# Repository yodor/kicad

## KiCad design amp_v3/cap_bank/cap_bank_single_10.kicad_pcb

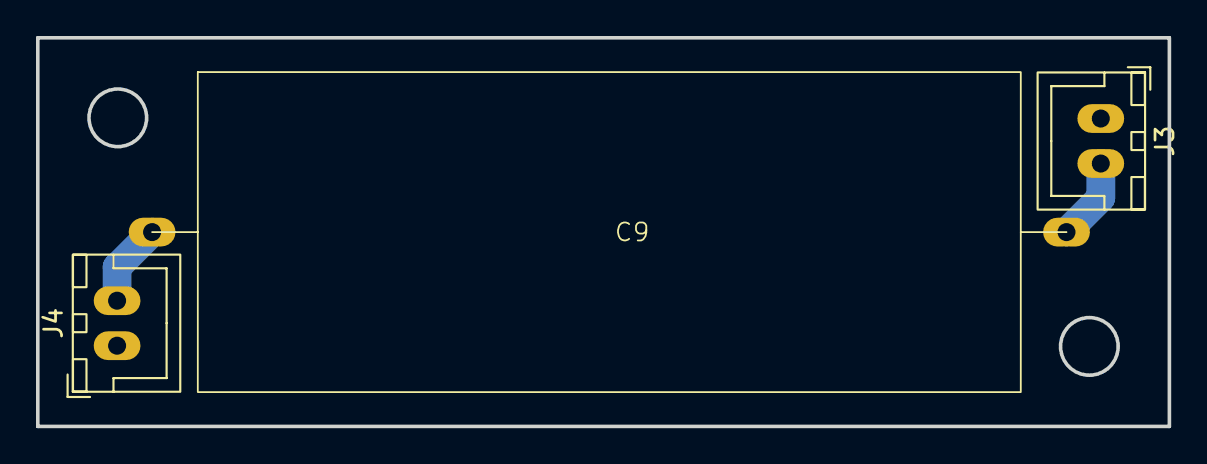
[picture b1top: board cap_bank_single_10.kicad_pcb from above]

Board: 2 copper layers, 62.9 x 21.6 mm, 3 parts (0 on the bottom side), 3 nets.

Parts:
C9: 10uF PP; 10uF - D18 - W46
J3: CAP_IN; JST_XH_B2B-XH-A_1x02_P2.50mm_Vertical
J4: CAP_OUT; JST_XH_B2B-XH-A_1x02_P2.50mm_Vertical

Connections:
/IN: C9.1, J3.2
/OUT: C9.2, J4.2
GNDA: J3.1, J4.1

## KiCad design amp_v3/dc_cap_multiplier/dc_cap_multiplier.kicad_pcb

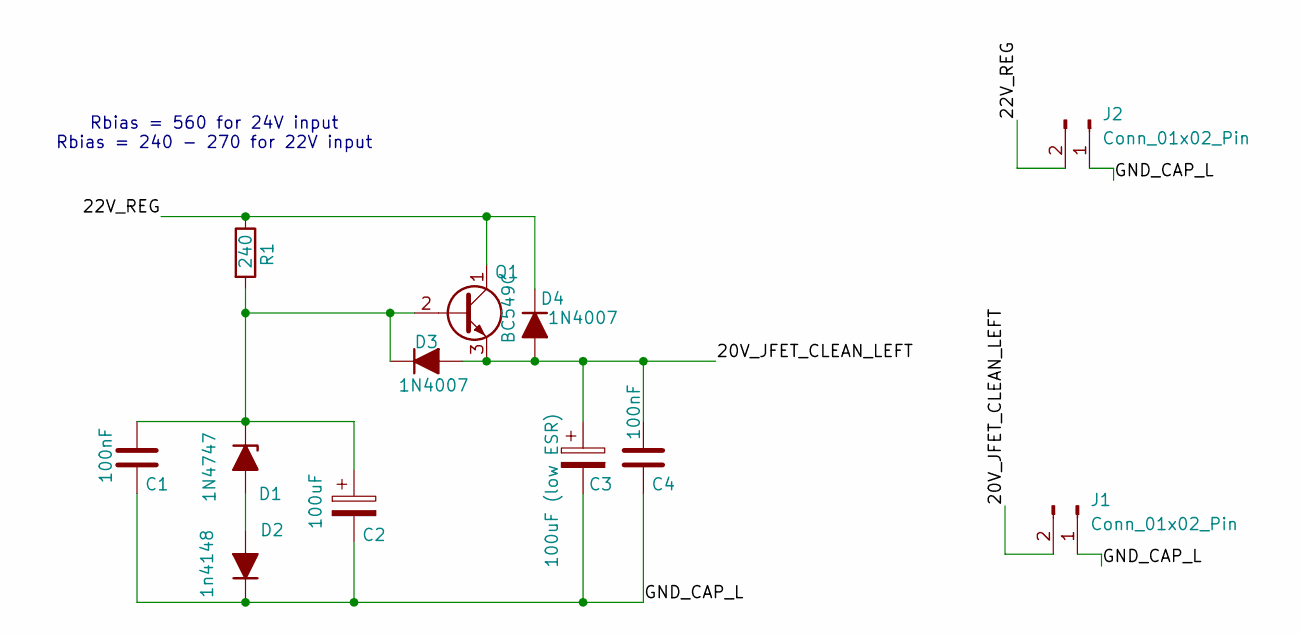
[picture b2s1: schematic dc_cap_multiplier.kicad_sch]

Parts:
C1, C4: 100nF; C_Rect_L7.0mm_W2.5mm_P5.00mm
C2: 100uF; CP_Radial_D6.3mm_P2.50mm
C3: 100uF (low ESR); CP_Radial_D5.0mm_P2.50mm
D1: 1N4747; D_A-405_P10.16mm_Horizontal
D2: 1n4148; D_A-405_P10.16mm_Horizontal
D3, D4: 1N4007; D_A-405_P10.16mm_Horizontal
J1, J2: Conn_01x02_Pin; JST_XH_B2B-XH-A_1x02_P2.50mm_Vertical
Q1: BC549C; TO-92_Inline_Wide
R1: 240; R_Axial_DIN0207_L6.3mm_D2.5mm_P7.62mm_Horizontal

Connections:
/20V_JFET_CLEAN_LEFT: C3.1, C4.1, D3.2 (A), D4.2 (A), J1.2, Q1.3 (E)
/22V_REG: D4.1 (K), J2.2, Q1.1 (C), R1.1
/GND_CAP_L: C1.2, C2.2, C3.2, C4.2, D2.1 (K), J1.1, J2.1
unnamed: D1.2 (A), D2.2 (A)
unnamed: C1.1, C2.1, D1.1 (K), D3.1 (K), Q1.2 (B), R1.2

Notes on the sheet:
Rbias = 560 for 24V input Rbias = 240 - 270 for 22V input

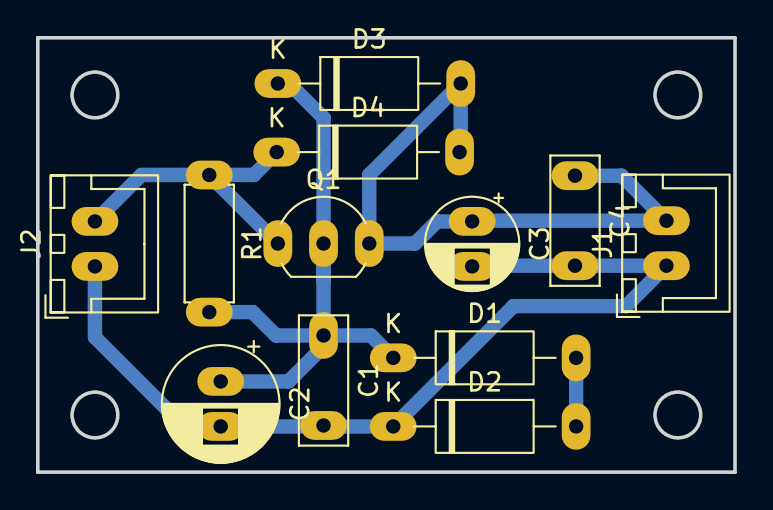
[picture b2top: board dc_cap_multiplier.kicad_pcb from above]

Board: 2 copper layers, 38.7 x 24.1 mm, 12 parts (0 on the bottom side), 5 nets.

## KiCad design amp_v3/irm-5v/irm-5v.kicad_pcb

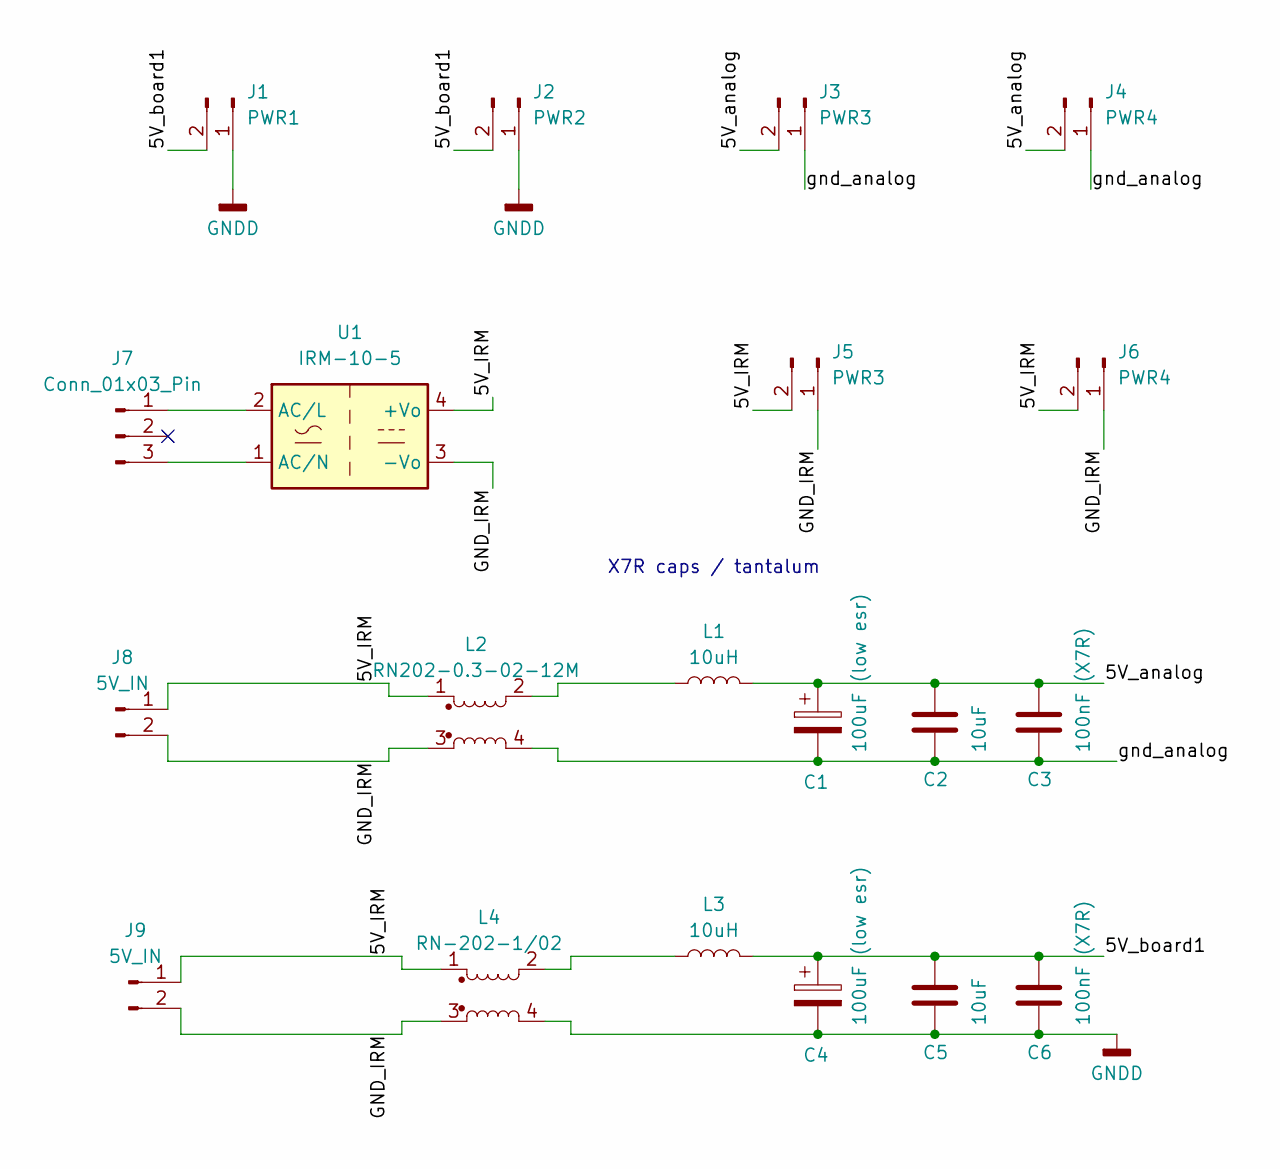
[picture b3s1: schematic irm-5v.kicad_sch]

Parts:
C1, C4: 100uF (low esr); CP_Radial_D6.3mm_P2.50mm
C2, C5: 10uF; C_Disc_D5.0mm_W2.5mm_P5.00mm
C3, C6: 100nF (X7R); C_Disc_D5.0mm_W2.5mm_P5.00mm
J1: PWR1; JST_XH_B2B-XH-A_1x02_P2.50mm_Vertical
J2: PWR2; JST_XH_B2B-XH-A_1x02_P2.50mm_Vertical
J3, J5: PWR3; JST_XH_B2B-XH-A_1x02_P2.50mm_Vertical
J4, J6: PWR4; JST_XH_B2B-XH-A_1x02_P2.50mm_Vertical
J7: Conn_01x03_Pin; JST_XH_B3B-XH-A_1x03_P2.50mm_Vertical
J8, J9: 5V_IN; JST_XH_B2B-XH-A_1x02_P2.50mm_Vertical
L1, L3: 10uH; L_Radial_D7.8mm_P5.00mm_Fastron_07HCP
L2: RN202-0.3-02-12M; Choke_Schaffner_RN202-04-8.8x18.2mm
L4: RN-202-1/02; Choke_Schaffner_RN202-04-8.8x18.2mm
U1: IRM-10-5; Converter_ACDC_MeanWell_IRM-10-xx_THT

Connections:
/5V power/5V_IRM: J5.2, J6.2, J8.1, J9.1, L2.1, L4.1, U1.4 (+Vo)
/5V power/5V_analog: C1.1, C2.1, C3.1, J3.2, J4.2, L1.2
/5V power/5V_board1: C4.1, C5.1, C6.1, J1.2, J2.2, L3.2
/5V power/GND_IRM: J5.1, J6.1, J8.2, J9.2, L2.3, L4.3, U1.3 (-Vo)
/5V power/gnd_analog: C1.2, C2.2, C3.2, J3.1, J4.1, L2.4
GNDD: C4.2, C5.2, C6.2, J1.1, J2.1, L4.4
unnamed: J7.1, U1.2 (AC/L)
unnamed: J7.3, U1.1 (AC/N)
unnamed: L1.1, L2.2
unnamed: L3.1, L4.2

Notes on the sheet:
X7R caps / tantalum

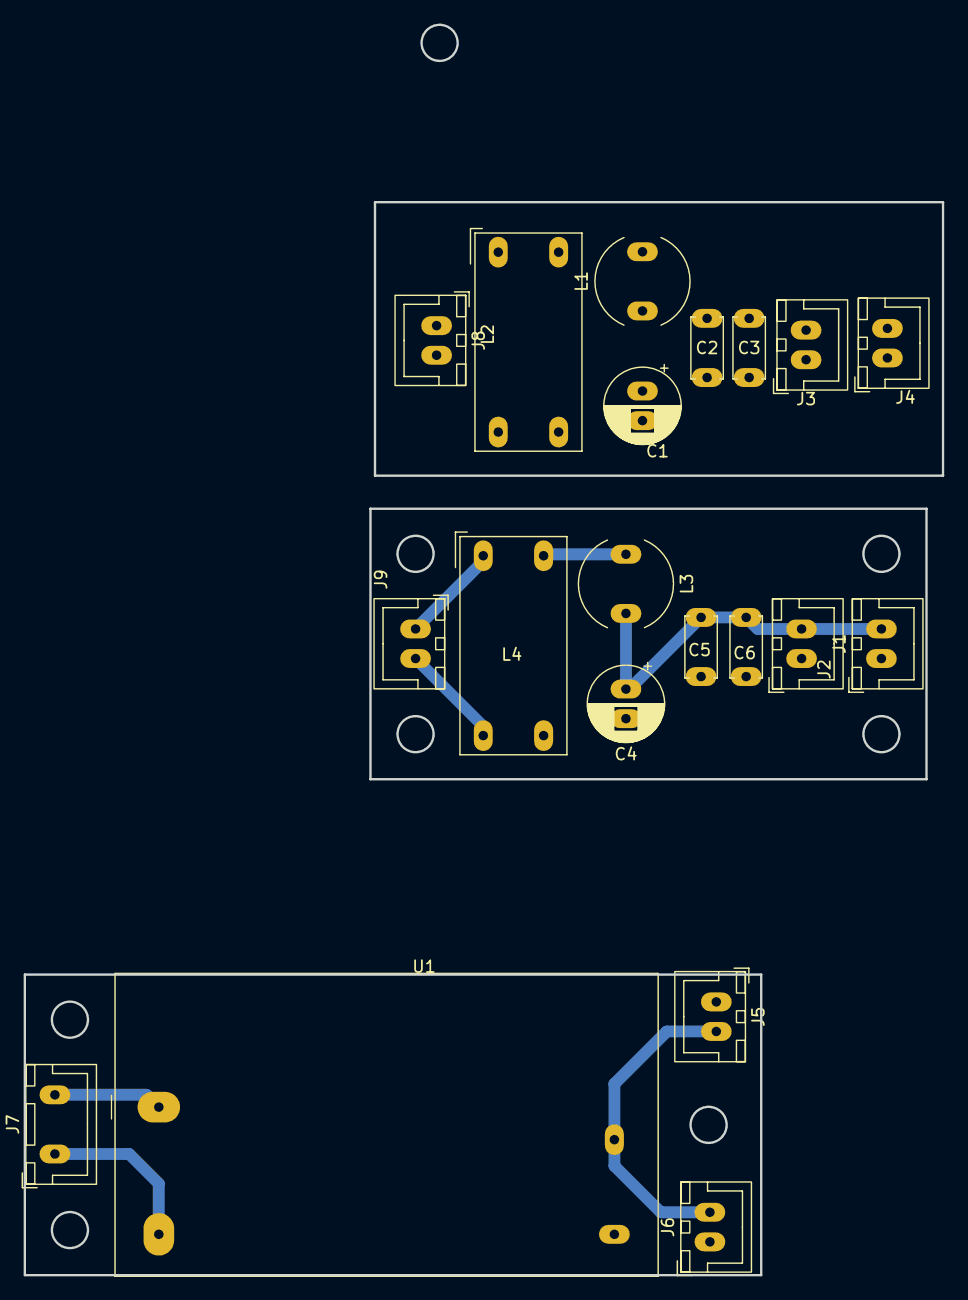
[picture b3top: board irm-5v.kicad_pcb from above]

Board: 2 copper layers, 77.6 x 105.7 mm, 20 parts (0 on the bottom side), 10 nets.

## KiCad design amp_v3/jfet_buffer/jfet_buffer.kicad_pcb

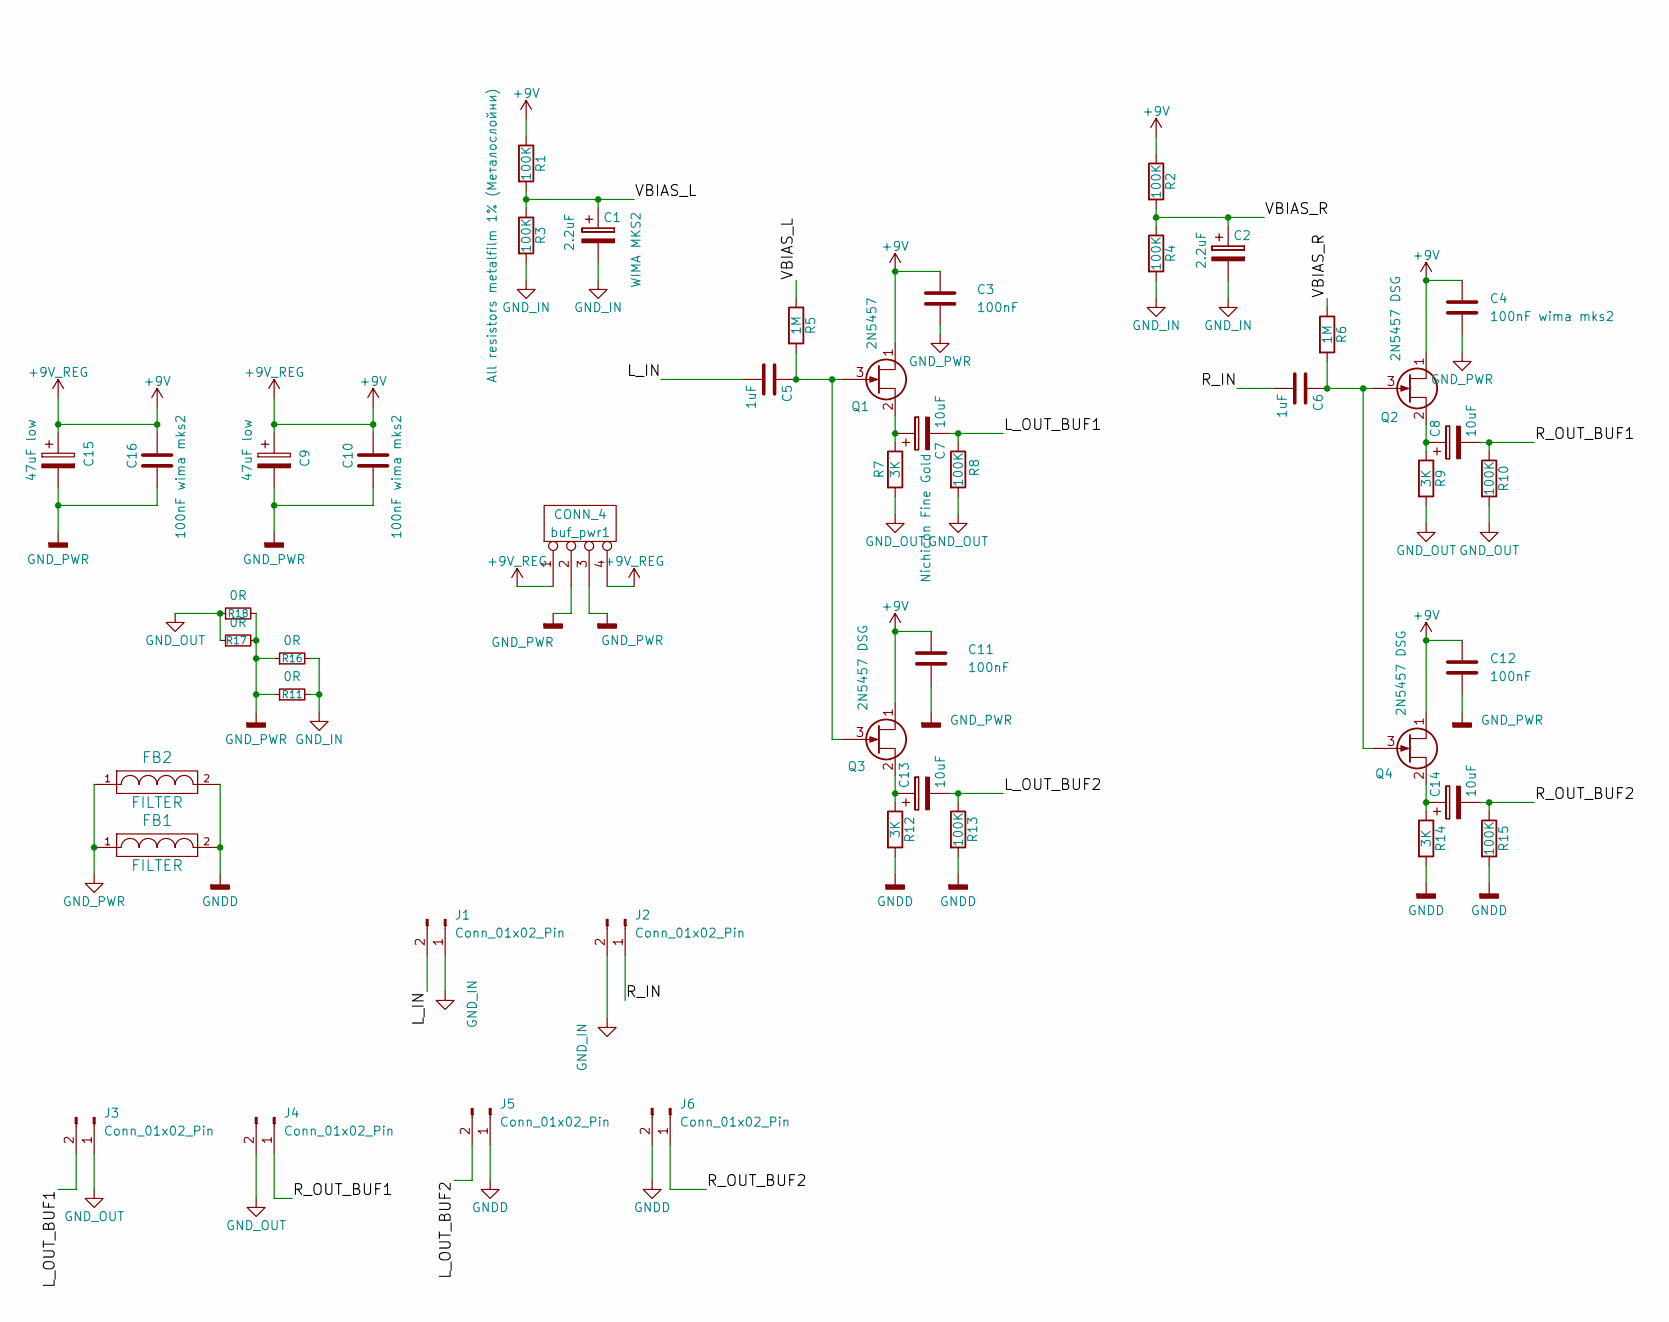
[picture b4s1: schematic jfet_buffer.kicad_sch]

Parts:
C1, C2: 2.2uF; C_Rect_L7.2mm_W7.2mm_P5.00mm_FKS2_FKP2_MKS2_MKP2
C3, C11, C12: 100nF; C_Rect_L7.2mm_W2.5mm_P5.00mm_FKS2_FKP2_MKS2_MKP2
C4, C10, C16: 100nF wima mks2; C_Rect_L7.2mm_W2.5mm_P5.00mm_FKS2_FKP2_MKS2_MKP2
C5, C6: 1uF; C_Rect_L7.2mm_W3.5mm_P5.00mm_FKS2_FKP2_MKS2_MKP2
C7, C8, C13, C14: 10uF; CP_Radial_D5.0mm_P2.50mm
C9, C15: 47uF low; CP_Radial_D5.0mm_P2.50mm
FB1, FB2: FILTER; R_Axial_DIN0309_L9.0mm_D3.2mm_P12.70mm_Horizontal
J1, J2, J3, J4, J5, J6: Conn_01x02_Pin; JST_XH_B2B-XH-A_1x02_P2.50mm_Vertical
Q1: 2N5457; TO-92L_Inline_Wide
Q2, Q3, Q4: 2N5457 DSG; TO-92L_Inline_Wide
R1, R2, R3, R4, R8, R10, R13, R15: 100K; R_Axial_DIN0309_L9.0mm_D3.2mm_P12.70mm_Horizontal
R5, R6: 1M; R_Axial_DIN0309_L9.0mm_D3.2mm_P12.70mm_Horizontal
R7, R9, R12, R14: 3K; R_Axial_DIN0309_L9.0mm_D3.2mm_P12.70mm_Horizontal
R11, R16, R17, R18: 0R; R_Axial_DIN0309_L9.0mm_D3.2mm_P12.70mm_Horizontal
buf_pwr1: CONN_4; JST_XH_B4B-XH-A_1x04_P2.50mm_Vertical

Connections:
+9V: C3.1, C4.1, C9.1, C10.1, C11.1, C12.1, C15.1, C16.1, Q1.1 (D), Q2.1 (D), Q3.1 (D), Q4.1 (D), R1.1, R2.1, buf_pwr1.1, buf_pwr1.4
/L_IN: C5.2, J1.2
/L_OUT_BUF1: C7.2, J3.2, R8.1
/L_OUT_BUF2: C13.2, J5.2, R13.1
/R_IN: C6.2, J2.1
/R_OUT_BUF1: C8.2, J4.1, R10.1
/R_OUT_BUF2: C14.2, J6.1, R15.1
/VBIAS_L: C1.1, R1.2, R3.1, R5.1
/VBIAS_R: C2.1, R2.2, R4.1, R6.1
GNDD: FB1.2, FB2.2, J5.1, J6.2, R12.2, R13.2, R14.2, R15.2
GND_IN: C1.2, C2.2, J1.1, J2.2, R3.2, R4.2, R11.2, R16.2
GND_OUT: J3.1, J4.2, R7.2, R8.2, R9.2, R10.2, R17.1, R18.1
GND_PWR: C3.2, C4.2, C9.2, C10.2, C11.2, C12.2, C15.2, C16.2, FB1.1, FB2.1, R11.1, R16.1, R17.2, R18.2, buf_pwr1.2, buf_pwr1.3
unnamed: C5.1, Q1.3 (G), Q3.3 (G), R5.2
unnamed: C7.1, Q1.2 (S), R7.1
unnamed: C6.1, Q2.3 (G), Q4.3 (G), R6.2
unnamed: C8.1, Q2.2 (S), R9.1
unnamed: C13.1, Q3.2 (S), R12.1
unnamed: C14.1, Q4.2 (S), R14.1

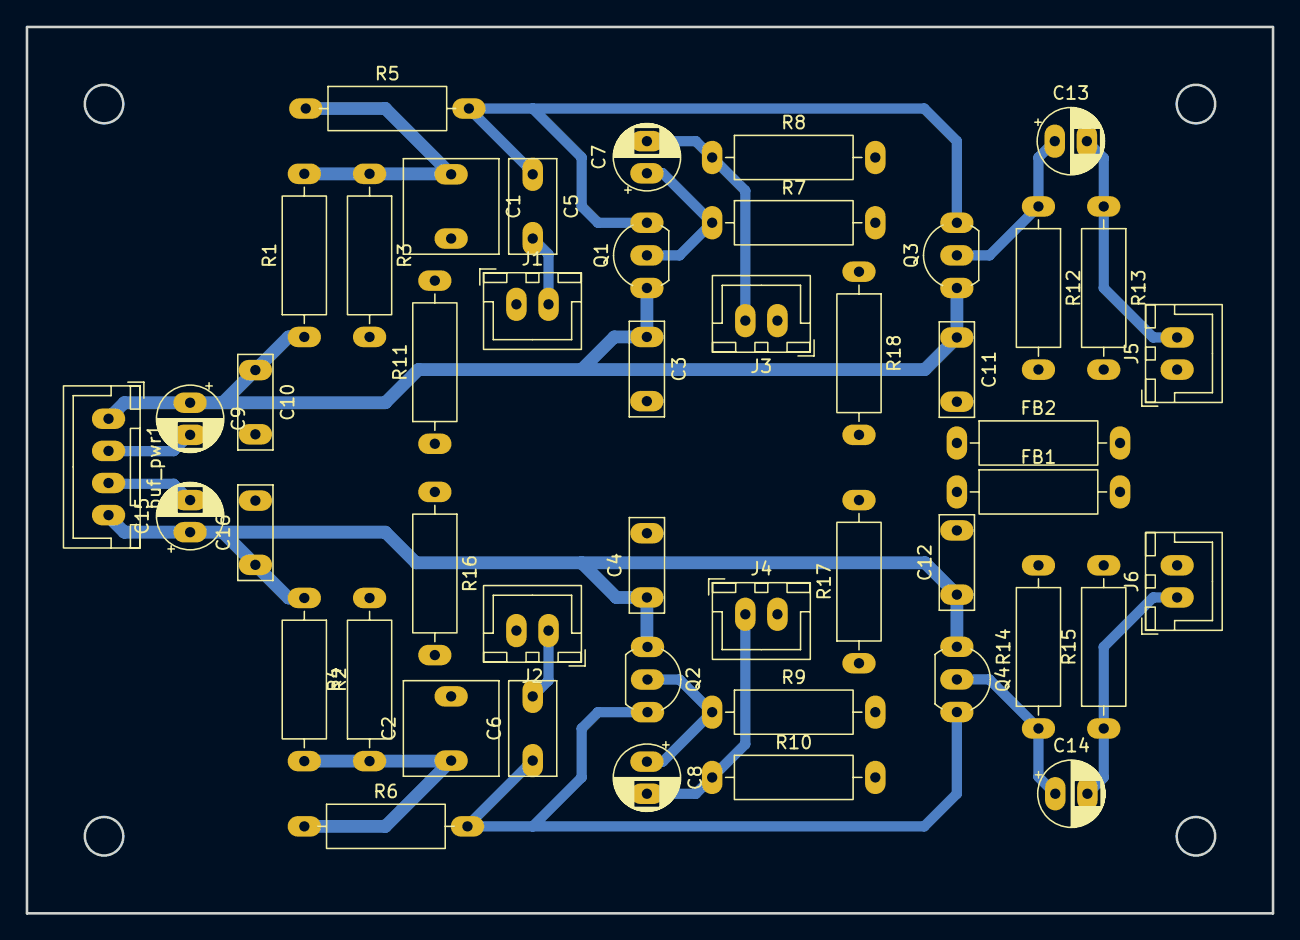
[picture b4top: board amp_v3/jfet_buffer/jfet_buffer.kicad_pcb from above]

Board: 2 copper layers, 97.0 x 69.0 mm, 47 parts (0 on the bottom side), 19 nets.

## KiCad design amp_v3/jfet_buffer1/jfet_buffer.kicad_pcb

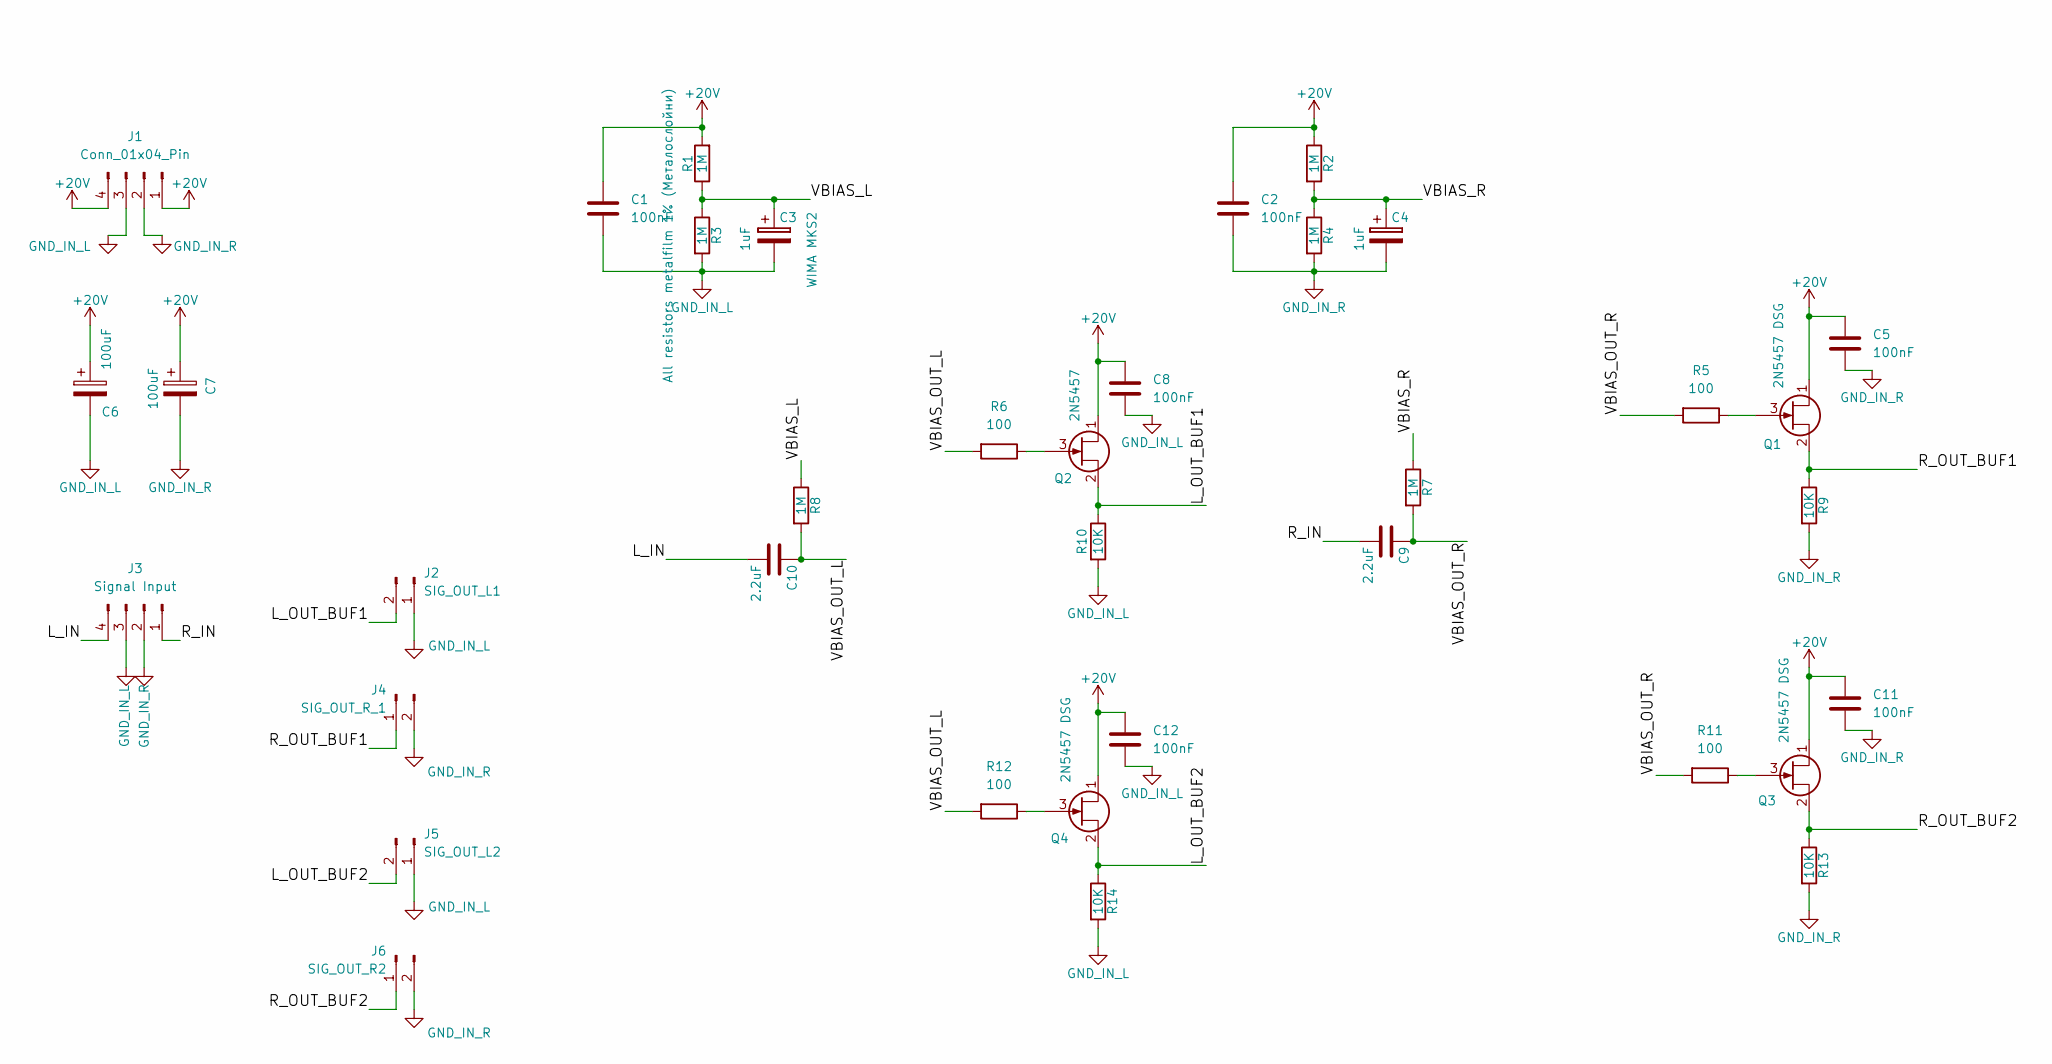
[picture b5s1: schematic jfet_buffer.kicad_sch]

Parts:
C1, C2, C5, C8, C11, C12: 100nF; C_Rect_L7.2mm_W2.5mm_P5.00mm_FKS2_FKP2_MKS2_MKP2
C3, C4: 1uF; C_Rect_L7.2mm_W3.5mm_P5.00mm_FKS2_FKP2_MKS2_MKP2
C6, C7: 100uF; CP_Radial_D5.0mm_P2.50mm
C9, C10: 2.2uF; C_Rect_L7.2mm_W7.2mm_P5.00mm_FKS2_FKP2_MKS2_MKP2
J1: Conn_01x04_Pin; JST_XH_B4B-XH-A_1x04_P2.50mm_Vertical
J2: SIG_OUT_L1; JST_XH_B2B-XH-A_1x02_P2.50mm_Vertical
J3: Signal Input; JST_XH_B4B-XH-A_1x04_P2.50mm_Vertical
J4: SIG_OUT_R_1; JST_XH_B2B-XH-A_1x02_P2.50mm_Vertical
J5: SIG_OUT_L2; JST_XH_B2B-XH-A_1x02_P2.50mm_Vertical
J6: SIG_OUT_R2; JST_XH_B2B-XH-A_1x02_P2.50mm_Vertical
Q1, Q3, Q4: 2N5457 DSG; TO-92L_Inline_Wide
Q2: 2N5457; TO-92L_Inline_Wide
R1, R2, R3, R4, R7, R8: 1M; R_Axial_DIN0207_L6.3mm_D2.5mm_P7.62mm_Horizontal
R5, R6: 100; R_Axial_DIN0207_L6.3mm_D2.5mm_P2.54mm_Vertical
R9, R10, R13, R14: 10K; R_Axial_DIN0207_L6.3mm_D2.5mm_P7.62mm_Horizontal
R11, R12: 100; R_Axial_DIN0207_L6.3mm_D2.5mm_P7.62mm_Horizontal

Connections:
+20V: C1.1, C2.1, C5.1, C6.1, C7.1, C8.1, C11.1, C12.1, J1.1, J1.4, Q1.1 (D), Q2.1 (D), Q3.1 (D), Q4.1 (D), R1.2, R2.1
/L_IN: C10.2, J3.4
/L_OUT_BUF1: J2.2, Q2.2 (S), R10.1
/L_OUT_BUF2: J5.2, Q4.2 (S), R14.1
/R_IN: C9.2, J3.1
/R_OUT_BUF1: J4.1, Q1.2 (S), R9.1
/R_OUT_BUF2: J6.1, Q3.2 (S), R13.1
/VBIAS_L: C3.1, R1.1, R3.1, R8.1
/VBIAS_OUT_L: C10.1, R6.2, R8.2, R12.2
/VBIAS_OUT_R: C9.1, R5.2, R7.2, R11.2
/VBIAS_R: C4.1, R2.2, R4.1, R7.1
GND_IN_L: C1.2, C3.2, C6.2, C8.2, C12.2, J1.3, J2.1, J3.3, J5.1, R3.2, R10.2, R14.2
GND_IN_R: C2.2, C4.2, C5.2, C7.2, C11.2, J1.2, J3.2, J4.2, J6.2, R4.2, R9.2, R13.2
unnamed: Q1.3 (G), R5.1
unnamed: Q2.3 (G), R6.1
unnamed: Q3.3 (G), R11.1
unnamed: Q4.3 (G), R12.1

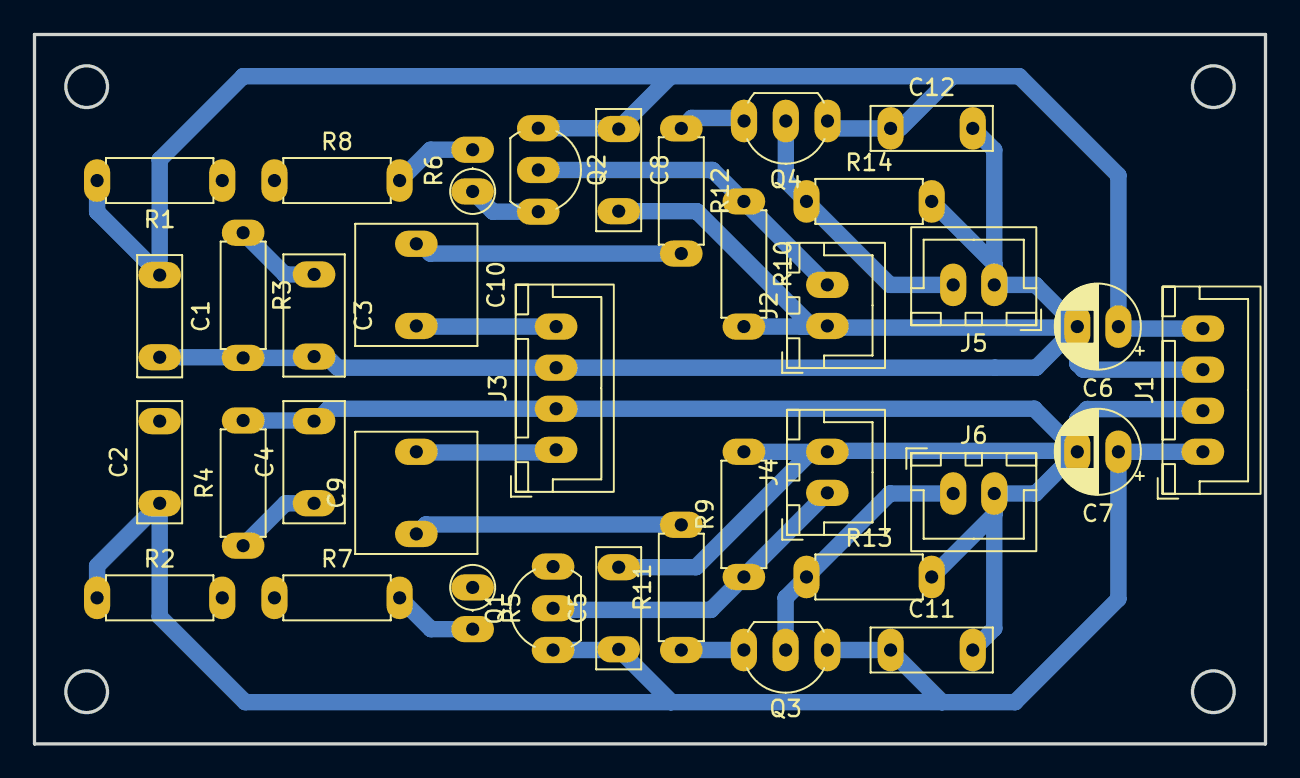
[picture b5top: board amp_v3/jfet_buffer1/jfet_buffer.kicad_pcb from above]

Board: 2 copper layers, 74.9 x 43.2 mm, 36 parts (0 on the bottom side), 17 nets.

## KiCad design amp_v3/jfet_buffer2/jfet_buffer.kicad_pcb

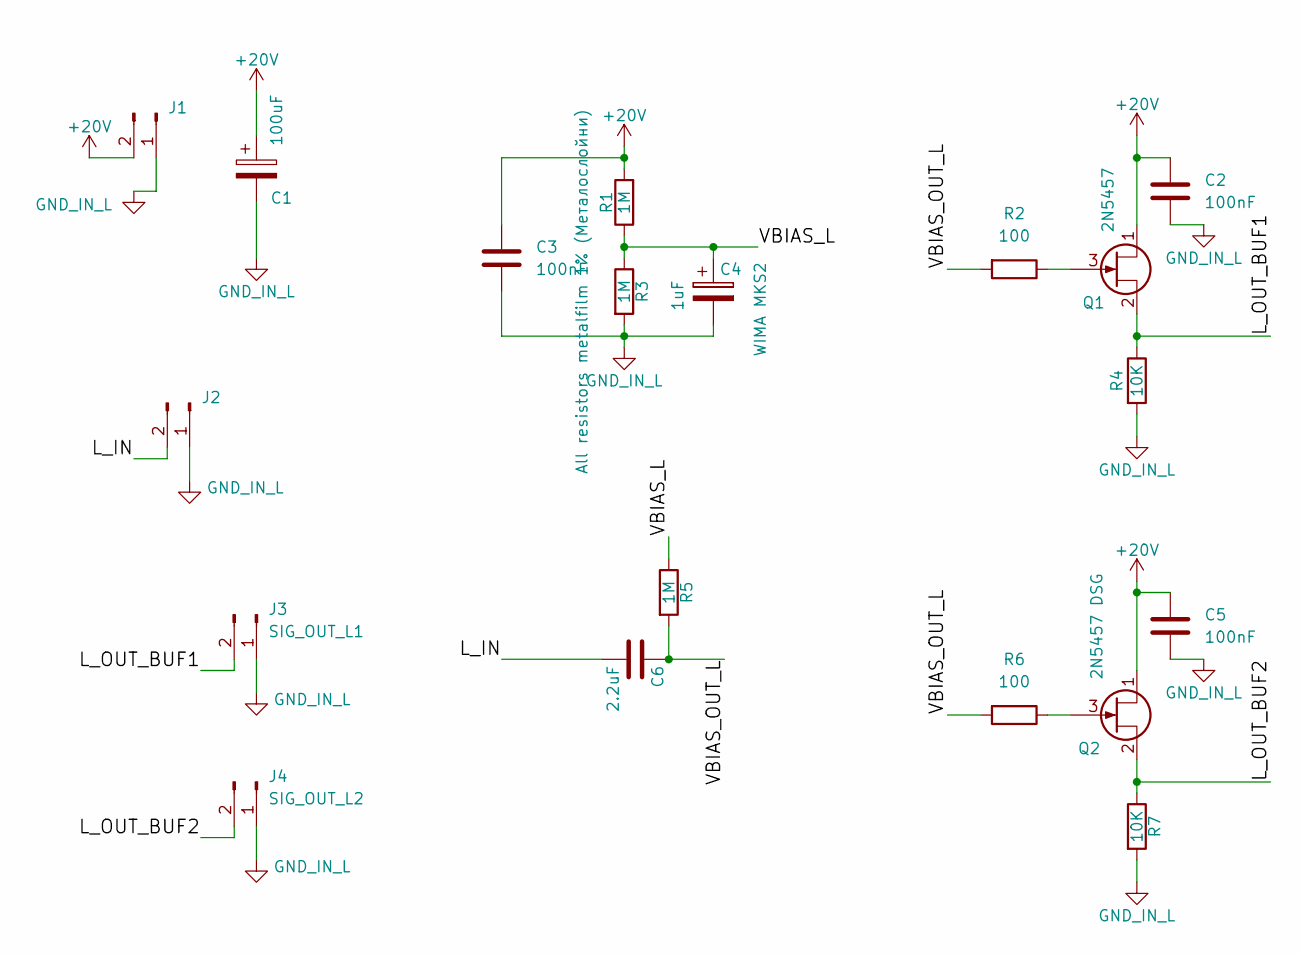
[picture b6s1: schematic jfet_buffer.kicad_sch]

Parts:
C1: 100uF; CP_Radial_D5.0mm_P2.50mm
C2, C3, C5: 100nF; C_Rect_L7.2mm_W2.5mm_P5.00mm_FKS2_FKP2_MKS2_MKP2
C4: 1uF; C_Rect_L7.2mm_W3.5mm_P5.00mm_FKS2_FKP2_MKS2_MKP2
C6: 2.2uF; C_Rect_L7.2mm_W7.2mm_P5.00mm_FKS2_FKP2_MKS2_MKP2
J1, J2, J3: SIG_OUT_L1; JST_XH_B2B-XH-A_1x02_P2.50mm_Vertical
J4: SIG_OUT_L2; JST_XH_B2B-XH-A_1x02_P2.50mm_Vertical
Q1: 2N5457; TO-92L_Inline_Wide
Q2: 2N5457 DSG; TO-92L_Inline_Wide
R1, R3, R5: 1M; R_Axial_DIN0207_L6.3mm_D2.5mm_P7.62mm_Horizontal
R2, R6: 100; R_Axial_DIN0207_L6.3mm_D2.5mm_P7.62mm_Horizontal
R4, R7: 10K; R_Axial_DIN0207_L6.3mm_D2.5mm_P7.62mm_Horizontal

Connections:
+20V: C1.1, C2.1, C3.1, C5.1, J1.2, Q1.1 (D), Q2.1 (D), R1.2; also elsewhere on the board
/L_IN: C6.2, J2.2
/L_OUT_BUF1: J3.2, Q1.2 (S), R4.1
/L_OUT_BUF2: J4.2, Q2.2 (S), R7.1
/VBIAS_L: C4.1, R1.1, R3.1, R5.1
/VBIAS_OUT_L: C6.1, R2.2, R5.2, R6.2
GND_IN_L: C1.2, C2.2, C3.2, C4.2, C5.2, J1.1, J2.1, J3.1, J4.1, R3.2, R4.2, R7.2
unnamed: Q1.3 (G), R2.1
unnamed: Q2.3 (G), R6.1

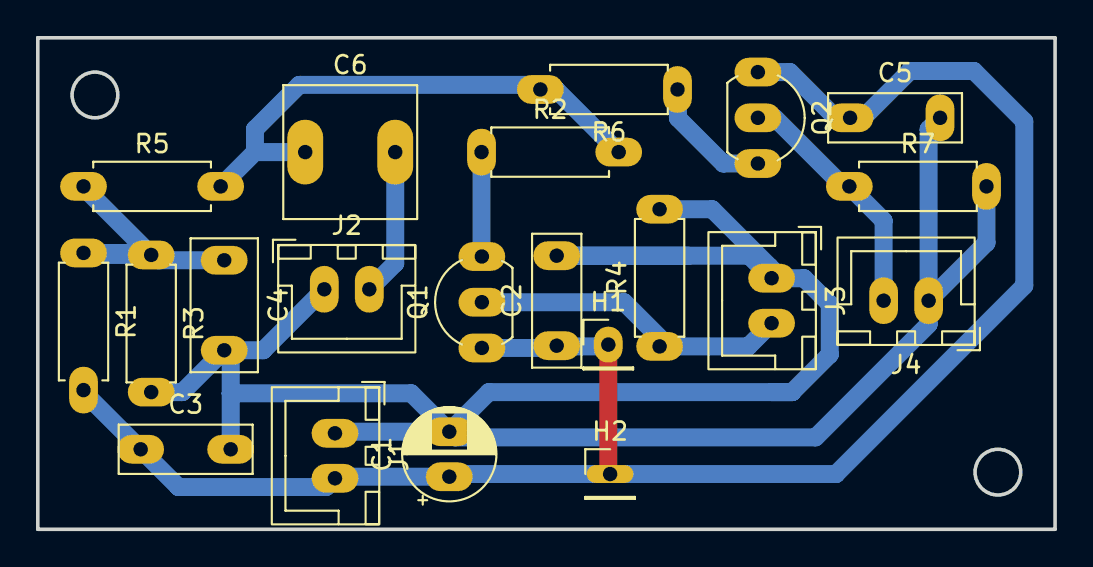
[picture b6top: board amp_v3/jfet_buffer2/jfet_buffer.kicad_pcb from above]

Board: 2 copper layers, 56.5 x 27.3 mm, 21 parts (0 on the bottom side), 9 nets.

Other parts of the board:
H1, H2: MountingHole_Pad; PinHeader_1x01_P2.54mm_Vertical

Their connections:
+20V: H1.1 (1_1), H2.1 (1_1); also elsewhere on the board
